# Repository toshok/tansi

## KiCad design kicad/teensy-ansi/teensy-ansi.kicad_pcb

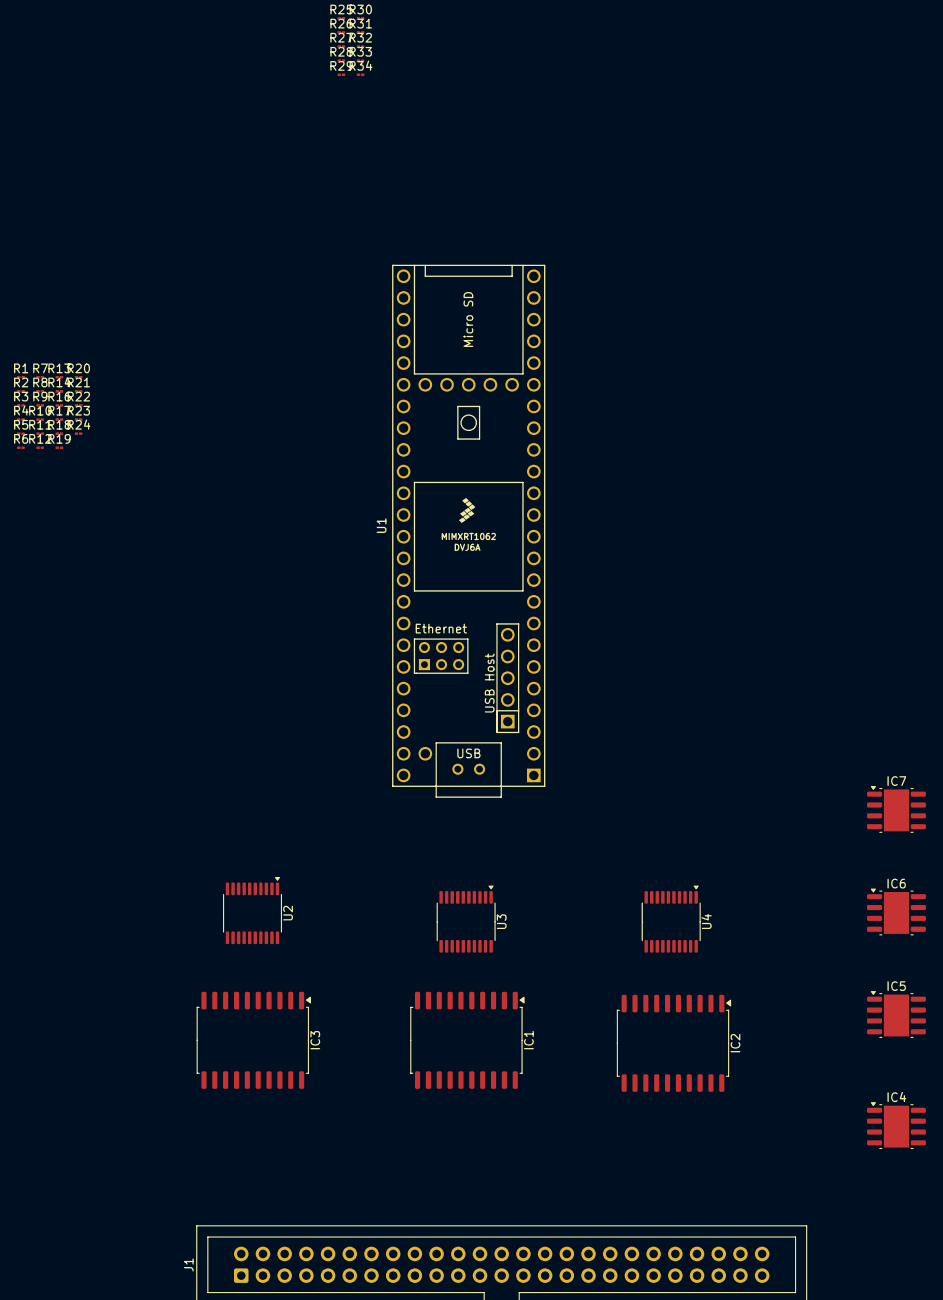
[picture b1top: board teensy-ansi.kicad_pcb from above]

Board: 2 copper layers, 45 parts (0 on the bottom side), 79 nets, no tracks yet.

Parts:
IC1, IC2, IC3: 74FCT621ATSOG; SOIC-20W_7.5x12.8mm_P1.27mm
IC4, IC5, IC6, IC7: SN75176BP; SOIC-8-1EP_3.9x4.9mm_P1.27mm_EP2.95x4.9mm_Mask2.71x3.4mm
J1: Conn_02x25_Odd_Even; IDC-Header_2x25_P2.54mm_Vertical
R1, R3, R5, R7, R9, R11, R13: 220 / 5%; R_01005_0402Metric
R2, R4, R6, R8, R10, R12, R14: 330 / %5; R_01005_0402Metric
R16: 10k / 10%; R_01005_0402Metric
R17, R18, R19, R20, R21, R22, R23, R24: 100 / 10%; R_01005_0402Metric
R25, R26, R27, R28, R29, R30, R31, R32, R33, R34: 150 / 10%; R_01005_0402Metric
U1: Teensy4.1; Teensy41
U2, U3, U4: TXS0108EPW; TSSOP-20_4.4x6.5mm_P0.65mm

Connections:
+3V3: U1.15 (3V3), U1.46 (3V3), U1.51 (3V3), U2.2 (VCCA), U3.2 (VCCA), U4.2 (VCCA)
+5V: IC1.20 (VCC), IC2.1 (GAB), IC2.19 (~GBA), IC2.20 (VCC), IC3.1 (GAB), IC3.20 (VCC), IC4.8 (VCC), IC5.8 (VCC), IC6.2 (~RE), IC6.3 (DE), IC6.8 (VCC), IC7.2 (~RE), IC7.3 (DE), IC7.8 (VCC), R1.1, R3.1, R5.1, R7.1, R9.1, R11.1, R13.1, R16.1, R25.2, U1.49 (VUSB), U2.10 (OE), U2.19 (VCCB), U3.10 (OE), U3.19 (VCCB), U4.10 (OE), U4.19 (VCCB)
/ansi_attention_3v: U1.28 (36_CS), U4.5 (A4)
/ansi_attention_5v: IC2.5 (A4), U4.16 (B4)
/ansi_bus_ack_3v: U1.25 (33_MCLK2), U4.1 (A1)
/ansi_bus_ack_5v: IC2.2 (A1), U4.20 (B1)
/ansi_bus_direction_3v: U1.22 (30_CRX3), U3.6 (A5)
/ansi_bus_direction_5v: IC1.4 (A3), U3.15 (B5)
/ansi_busy_3v: U1.29 (37_CS), U4.6 (A5)
/ansi_busy_5v: IC2.6 (A5), U4.15 (B5)
/ansi_cb0_3v: U1.2 (0_RX1_CRX2_CS1), U2.9 (A8)
/ansi_cb0_5v: IC3.9 (A8), U2.12 (B8)
/ansi_cb1_3v: U1.6 (4_BCLK2), U2.5 (A4)
/ansi_cb1_5v: IC3.5 (A4), U2.16 (B4)
/ansi_cb2_3v: U1.3 (1_TX1_CTX2_MISO1), U2.8 (A7)
/ansi_cb2_5v: IC3.8 (A7), U2.13 (B7)
/ansi_cb3_3v: U1.7 (5_IN2), U2.4 (A3)
/ansi_cb3_5v: IC3.4 (A3), U2.17 (B3)
/ansi_cb4_3v: U1.4 (2_OUT2), U2.7 (A6)
/ansi_cb4_5v: IC3.7 (A6), U2.14 (B6)
/ansi_cb5_3v: U1.8 (6_OUT1D), U2.3 (A2)
/ansi_cb5_5v: IC3.3 (A2), U2.18 (B2)
/ansi_cb6_3v: U1.5 (3_LRCLK2), U2.6 (A5)
/ansi_cb6_5v: IC3.6 (A5), U2.15 (B5)
/ansi_cb7_3v: U1.9 (7_RX2_OUT1A), U2.1 (A1)
/ansi_cb7_5v: IC3.2 (A1), U2.20 (B1)
/ansi_command_req_3v: U1.20 (28_RX7), U3.8 (A7)
/ansi_command_req_5v: IC1.6 (A5), U3.13 (B7)
/ansi_index_3v: U1.26 (34_RX8), U4.3 (A2)
/ansi_index_5v: IC2.3 (A2), U4.18 (B2)
/ansi_param_req_3v: U1.21 (29_TX7), U3.7 (A6)
/ansi_param_req_5v: IC1.5 (A4), U3.14 (B6)
/ansi_port_enable_3v: U1.33 (41_A17), U4.7 (A6)
/ansi_port_enable_5v: IC1.8 (A7), U4.14 (B6)
/ansi_read_data_3v: U1.36 (14_A0_TX3_SPDIF_OUT), U4.9 (A8)
/ansi_read_data_5v: IC7.4 (D), U4.12 (B8)
/ansi_read_gate_3v: U1.23 (31_CTX3), U3.5 (A4)
/ansi_read_gate_5v: IC1.3 (A2), U3.16 (B4)
/ansi_read_ref_clock_3v: U1.37 (15_A1_RX3_SPDIF_IN), U4.8 (A7)
/ansi_read_ref_clock_5v: IC6.4 (D), U4.13 (B7)
/ansi_sector_mark_3v: U1.27 (35_TX8), U4.4 (A3)
/ansi_sector_mark_5v: IC2.4 (A3), U4.17 (B3)
/ansi_select_out_attn_in_3v: U1.19 (27_A13_SCK1), U3.9 (A8)
/ansi_select_out_attn_in_5v: IC1.7 (A6), U3.12 (B8)
/ansi_write_clock_3v: U1.39 (17_A3_TX4_SDA1), U3.1 (A1)
/ansi_write_clock_5v: IC4.1 (R), U3.20 (B1)
/ansi_write_data_3v: U1.38 (16_A2_RX4_SCL1), U3.3 (A2)
/ansi_write_data_5v: IC5.1 (R), U3.18 (B2)
/ansi_write_gate_3v: U1.24 (32_OUT1B), U3.4 (A3)
/ansi_write_gate_5v: IC1.2 (A1), U3.17 (B3)
/cable_attention: IC2.15 (B4), J1.35
/cable_bus_ack: IC2.18 (B1), J1.29
/cable_bus_direction: IC1.16 (B3), J1.19, R1.2, R2.1
/cable_busy: IC2.14 (B5), J1.37
/cable_cb0: IC3.11 (B8), J1.2
/cable_cb1: IC3.15 (B4), J1.3
/cable_cb2: IC3.12 (B7), J1.4
/cable_cb3: IC3.16 (B3), J1.5
/cable_cb4: IC3.13 (B6), J1.6
/cable_cb5: IC3.17 (B2), J1.7
/cable_cb6: IC3.14 (B5), J1.8
/cable_cb7: IC3.18 (B1), J1.9
/cable_command_req: IC1.14 (B5), J1.15, R9.2, R10.1
/cable_index: IC2.17 (B2), J1.31
/cable_param_req: IC1.15 (B4), J1.17, R11.2, R12.1
/cable_port_enable: IC1.12 (B7), J1.21, R13.2, R14.1, R16.2, R26.2
/cable_read_data_d+: IC7.6 (A), J1.39, R24.1
/cable_read_data_d-: IC7.7 (B), J1.40, R23.1
/cable_read_gate: IC1.17 (B2), J1.25, R3.2, R4.1
/cable_read_ref_clock_d+: IC6.6 (A), J1.42, R22.1
/cable_read_ref_clock_d-: IC6.7 (B), J1.43, R21.1
/cable_sector_mark: IC2.16 (B3), J1.33
/cable_select_out_attn_in: IC1.13 (B6), J1.13, R7.2, R8.1
/cable_write_clock_d+: IC4.6 (A), J1.45, R18.1
/cable_write_clock_d-: IC4.7 (B), J1.46, R17.1
/cable_write_data_d+: IC5.6 (A), J1.48, R20.1
/cable_write_data_d-: IC5.7 (B), J1.49, R19.1
/cable_write_gate: IC1.18 (B1), J1.27, R5.2, R6.1
GND: IC1.1 (GAB), IC1.10 (GND), IC1.19 (~GBA), IC2.10 (GND), IC3.10 (GND), IC3.19 (~GBA), IC4.2 (~RE), IC4.3 (DE), IC4.5 (GND), IC5.2 (~RE), IC5.3 (DE), IC5.5 (GND), IC6.5 (GND), IC7.5 (GND), J1.1, J1.10, J1.12, J1.14, J1.16, J1.18, J1.20, J1.22, J1.24, J1.26, J1.28, J1.30, J1.32, J1.34, J1.36, J1.38, J1.41, J1.44, J1.47, J1.50, R2.2, R4.2, R6.2, R8.2, R10.2, R12.2, R14.2, R17.2, R18.2, R19.2, R20.2, R21.2, R22.2, R23.2, R24.2, U1.1 (GND), U1.34 (GND), U1.47 (GND), U1.52 (GND), U2.11 (GND), U3.11 (GND), U4.11 (GND)

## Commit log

2024-05-06 phew. okay things look like they're initializing properly. time to start wiring things up
2024-05-19 I _think_ we're nearly done with the schematic
2024-05-19 more state machine/platform futzing
2024-06-16 some minor futzing
2024-06-16 bunch more work
2024-06-16 clang-format everything so I can stop having to worry about it
2024-06-24 clean up the pin read/write code. rename read_out_pins to sample_out_pins, and we now assume that the control bus pins will be readable/writable ahead of time (we set their direction when sampling th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
2024-06-24 biggest change is routing ansi_bus_direction_out_5v into GBA/GAB of the control bus transceiver
2024-09-25 all the lingering changes I have outstanding
2024-09-27 disable clang-format for the enum members
